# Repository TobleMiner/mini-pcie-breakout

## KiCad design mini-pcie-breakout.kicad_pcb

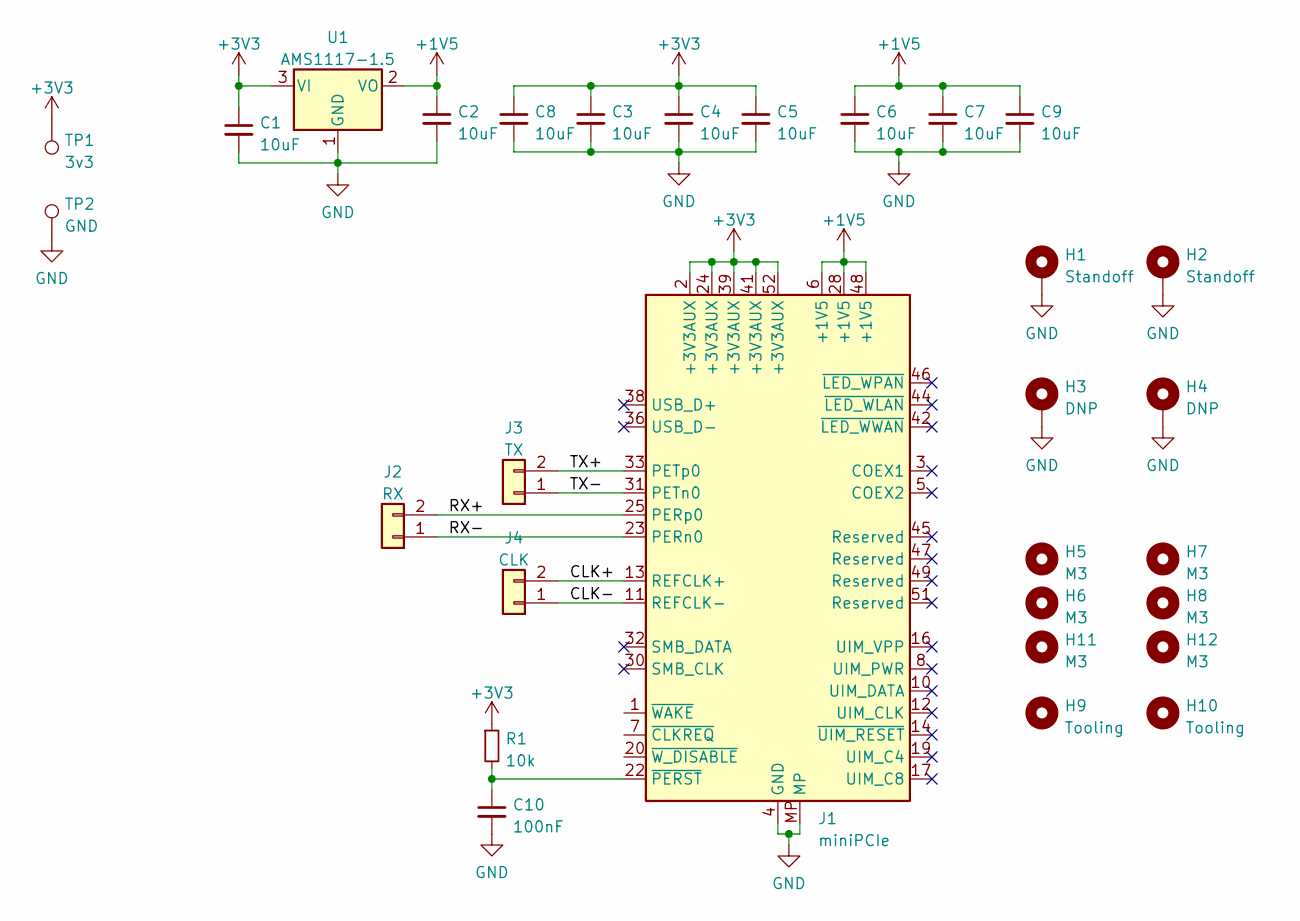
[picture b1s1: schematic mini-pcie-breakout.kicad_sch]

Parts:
C1, C2, C3, C4, C5, C6, C7, C8, C9: 10uF; C_0402_1005Metric; LCSC C15525
C10: 100nF; C_0402_1005Metric; LCSC C1525
H1, H2: Standoff; SMTSO25xx; LCSC C2915631
H3, H4: DNP; SMTSO25xx
H5, H6, H7, H8, H11, H12: M3; MountingHole_3.2mm_M3
H9, H10: Tooling; ToolingHole_JLCSMT
J1: miniPCIe; BUS_PCI_Express_Mini_Dual; LCSC C444927
J2: RX; Pad_1x02
J3: TX; Pad_1x02
J4: CLK; Pad_1x02
R1: 10k; R_0402_1005Metric; LCSC C25744
TP1: 3v3; TestPoint_Pad_2.0x2.0mm
TP2: GND; TestPoint_Pad_2.0x2.0mm
U1: AMS1117-1.5; SOT-223-3_TabPin2; LCSC C347219

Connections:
+1V5: C2.1, C6.1, C7.1, C9.1, J1.6 (+1V5), J1.28 (+1V5), J1.48 (+1V5), U1.2 (VO)
+3V3: C1.1, C3.1, C4.1, C5.1, C8.1, J1.2 (+3V3AUX), J1.24 (+3V3AUX), J1.39 (+3V3AUX), J1.41 (+3V3AUX), J1.52 (+3V3AUX), R1.1, TP1.1, U1.3 (VI)
/CLK+: J1.13 (REFCLK+), J4.2
/CLK-: J1.11 (REFCLK-), J4.1
/RX+: J1.25 (PERp0), J2.2
/RX-: J1.23 (PERn0), J2.1
/TX+: J1.33 (PETp0), J3.2
/TX-: J1.31 (PETn0), J3.1
GND: C1.2, C2.2, C3.2, C4.2, C5.2, C6.2, C7.2, C8.2, C9.2, C10.2, H1.1, H2.1, H3.1, H4.1, J1.4 (GND), J1.9 (GND), J1.15 (GND), J1.18 (GND), J1.21 (GND), J1.26 (GND), J1.27 (GND), J1.29 (GND), J1.34 (GND), J1.35 (GND), J1.37 (GND), J1.40 (GND), J1.43 (GND), J1.50 (GND), J1.MP, TP2.1, U1.1 (GND)
unnamed: C10.1, J1.22 (~PERST), R1.2

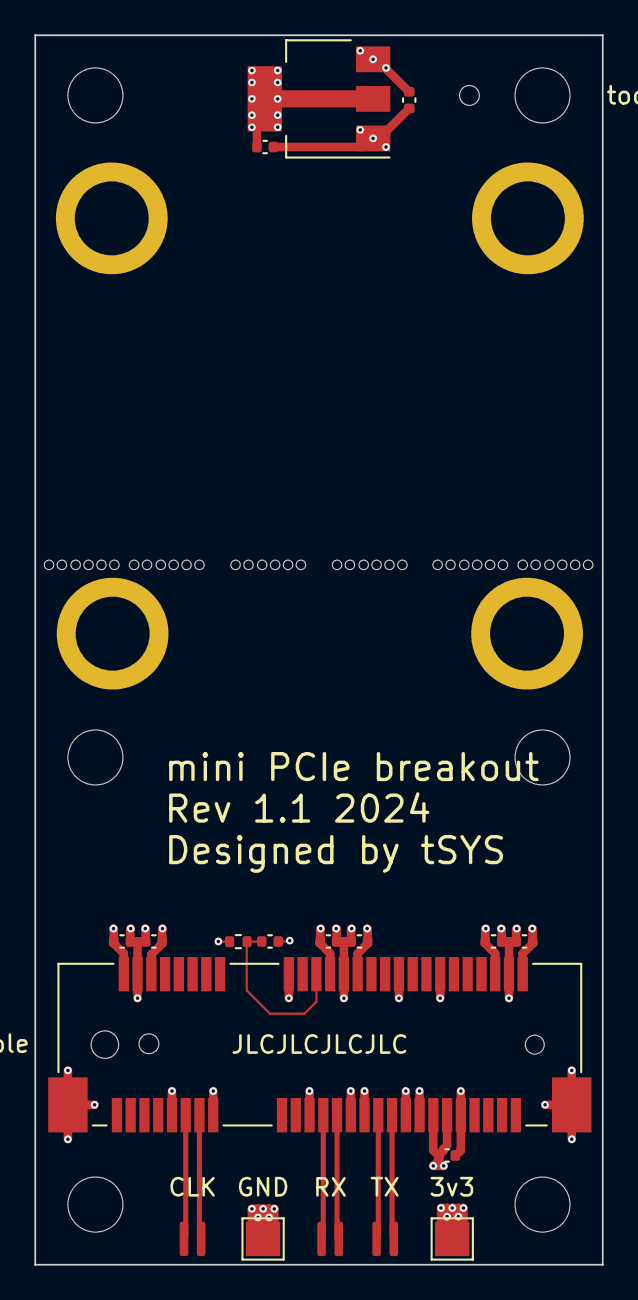
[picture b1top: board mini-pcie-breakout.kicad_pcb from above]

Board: 4 copper layers, 33.0 x 71.5 mm, 30 parts (0 on the bottom side), 10 nets.

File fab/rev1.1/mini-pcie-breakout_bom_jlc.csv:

"Comment","Designator","Footprint","LCSC Part #"
"10uF","C1,C2,C3,C4,C5,C6,C7,C8,C9","C_0402_1005Metric","C15525"
"100nF","C10","C_0402_1005Metric","C1525"
"Standoff","H1,H2","SMTSO25xx","C2915631"
"miniPCIe","J1","BUS_PCI_Express_Mini_Dual","C444927"
"10k","R1","R_0402_1005Metric","C25744"
"AMS1117-1.5","U1","SOT-223-3_TabPin2","C347219"

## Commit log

2024-03-16 Update JLC fab lib to include mousebites
2024-03-16 Add half-size mini PCIe support
